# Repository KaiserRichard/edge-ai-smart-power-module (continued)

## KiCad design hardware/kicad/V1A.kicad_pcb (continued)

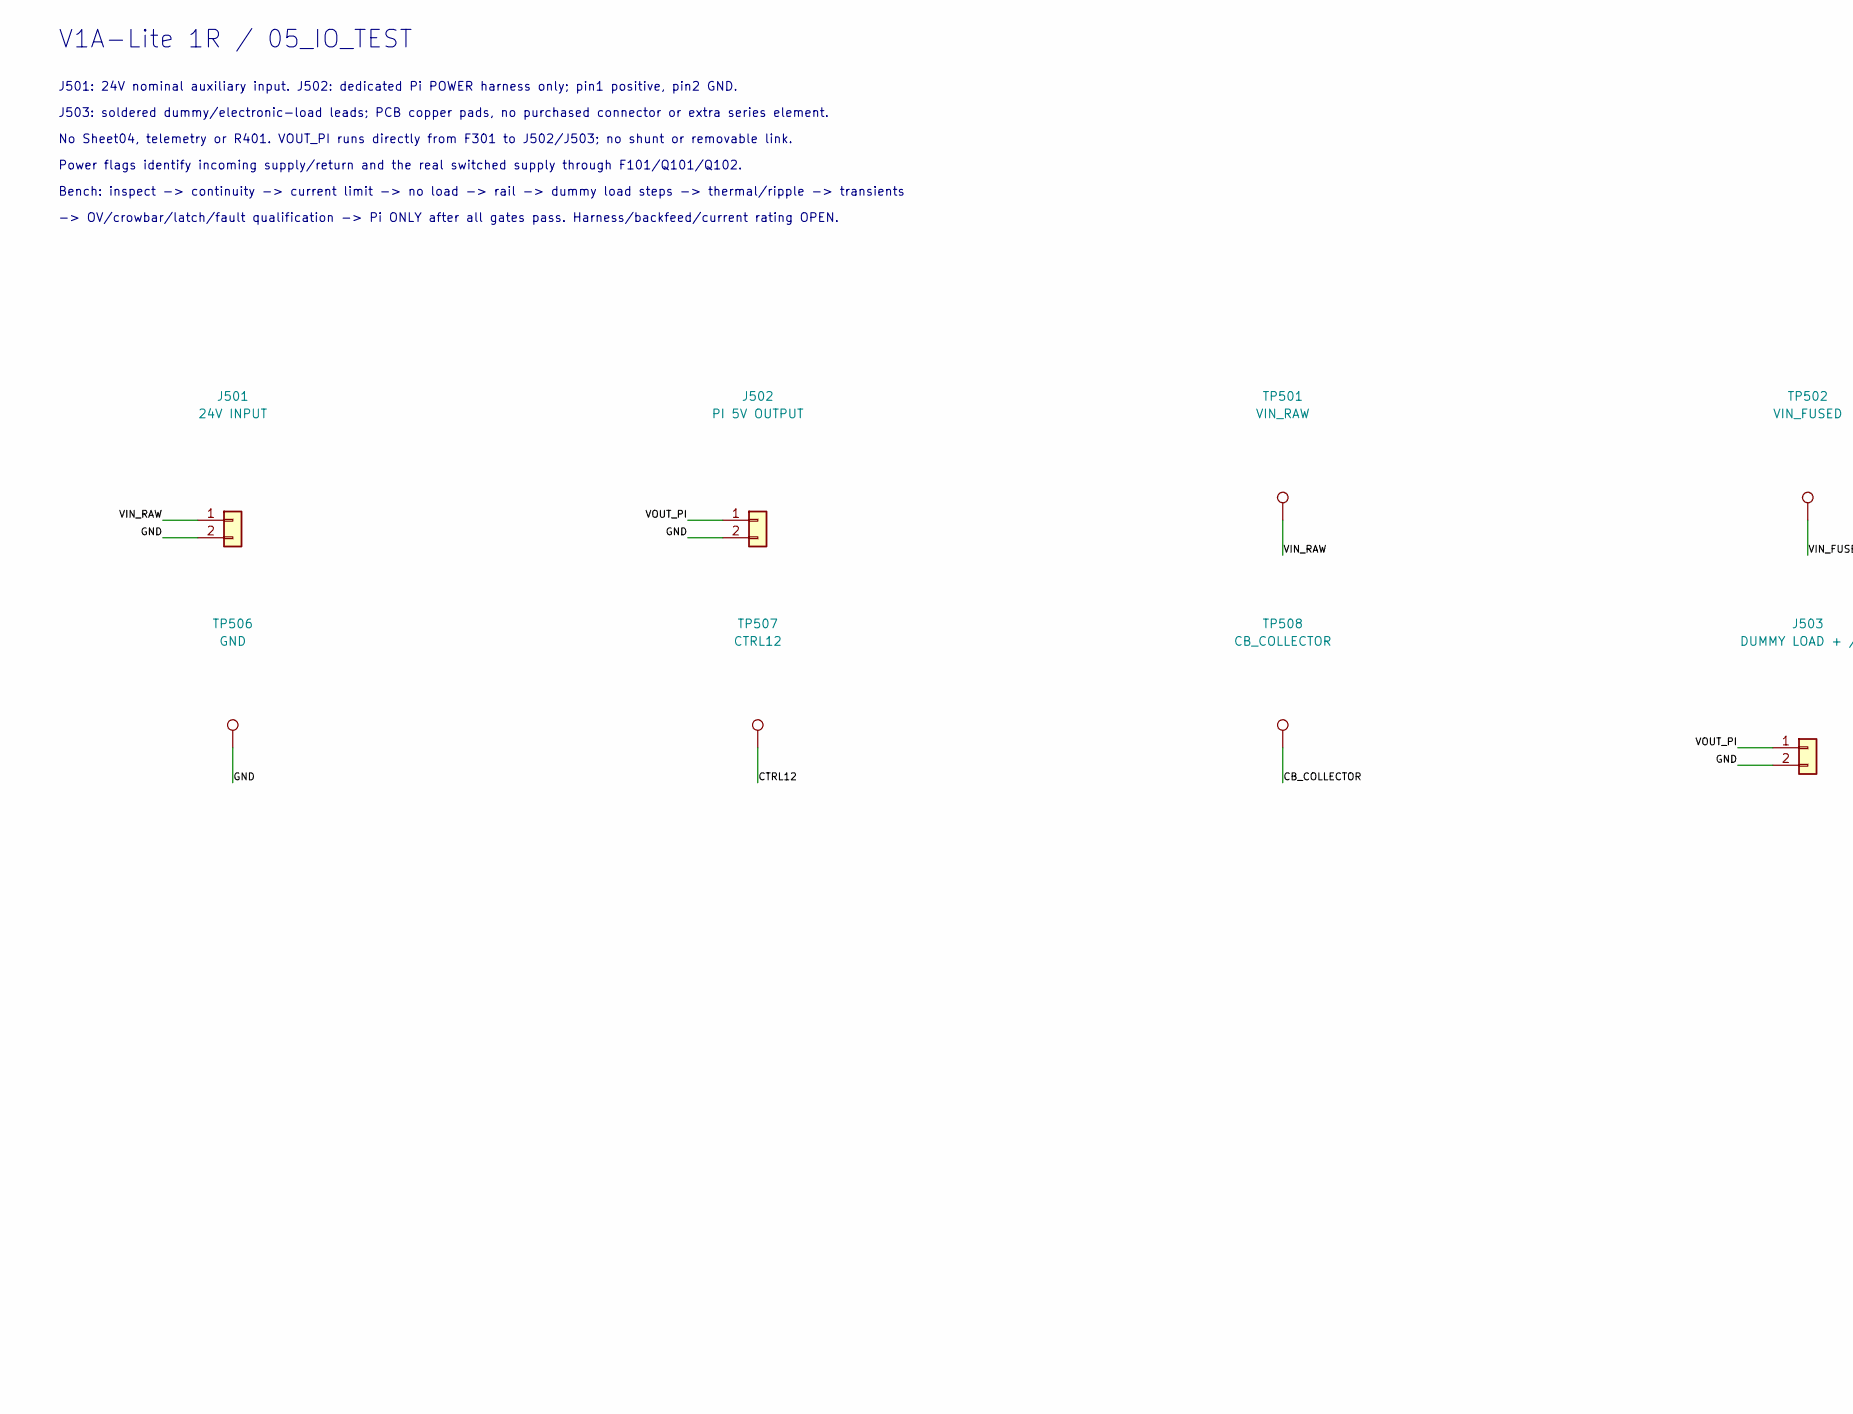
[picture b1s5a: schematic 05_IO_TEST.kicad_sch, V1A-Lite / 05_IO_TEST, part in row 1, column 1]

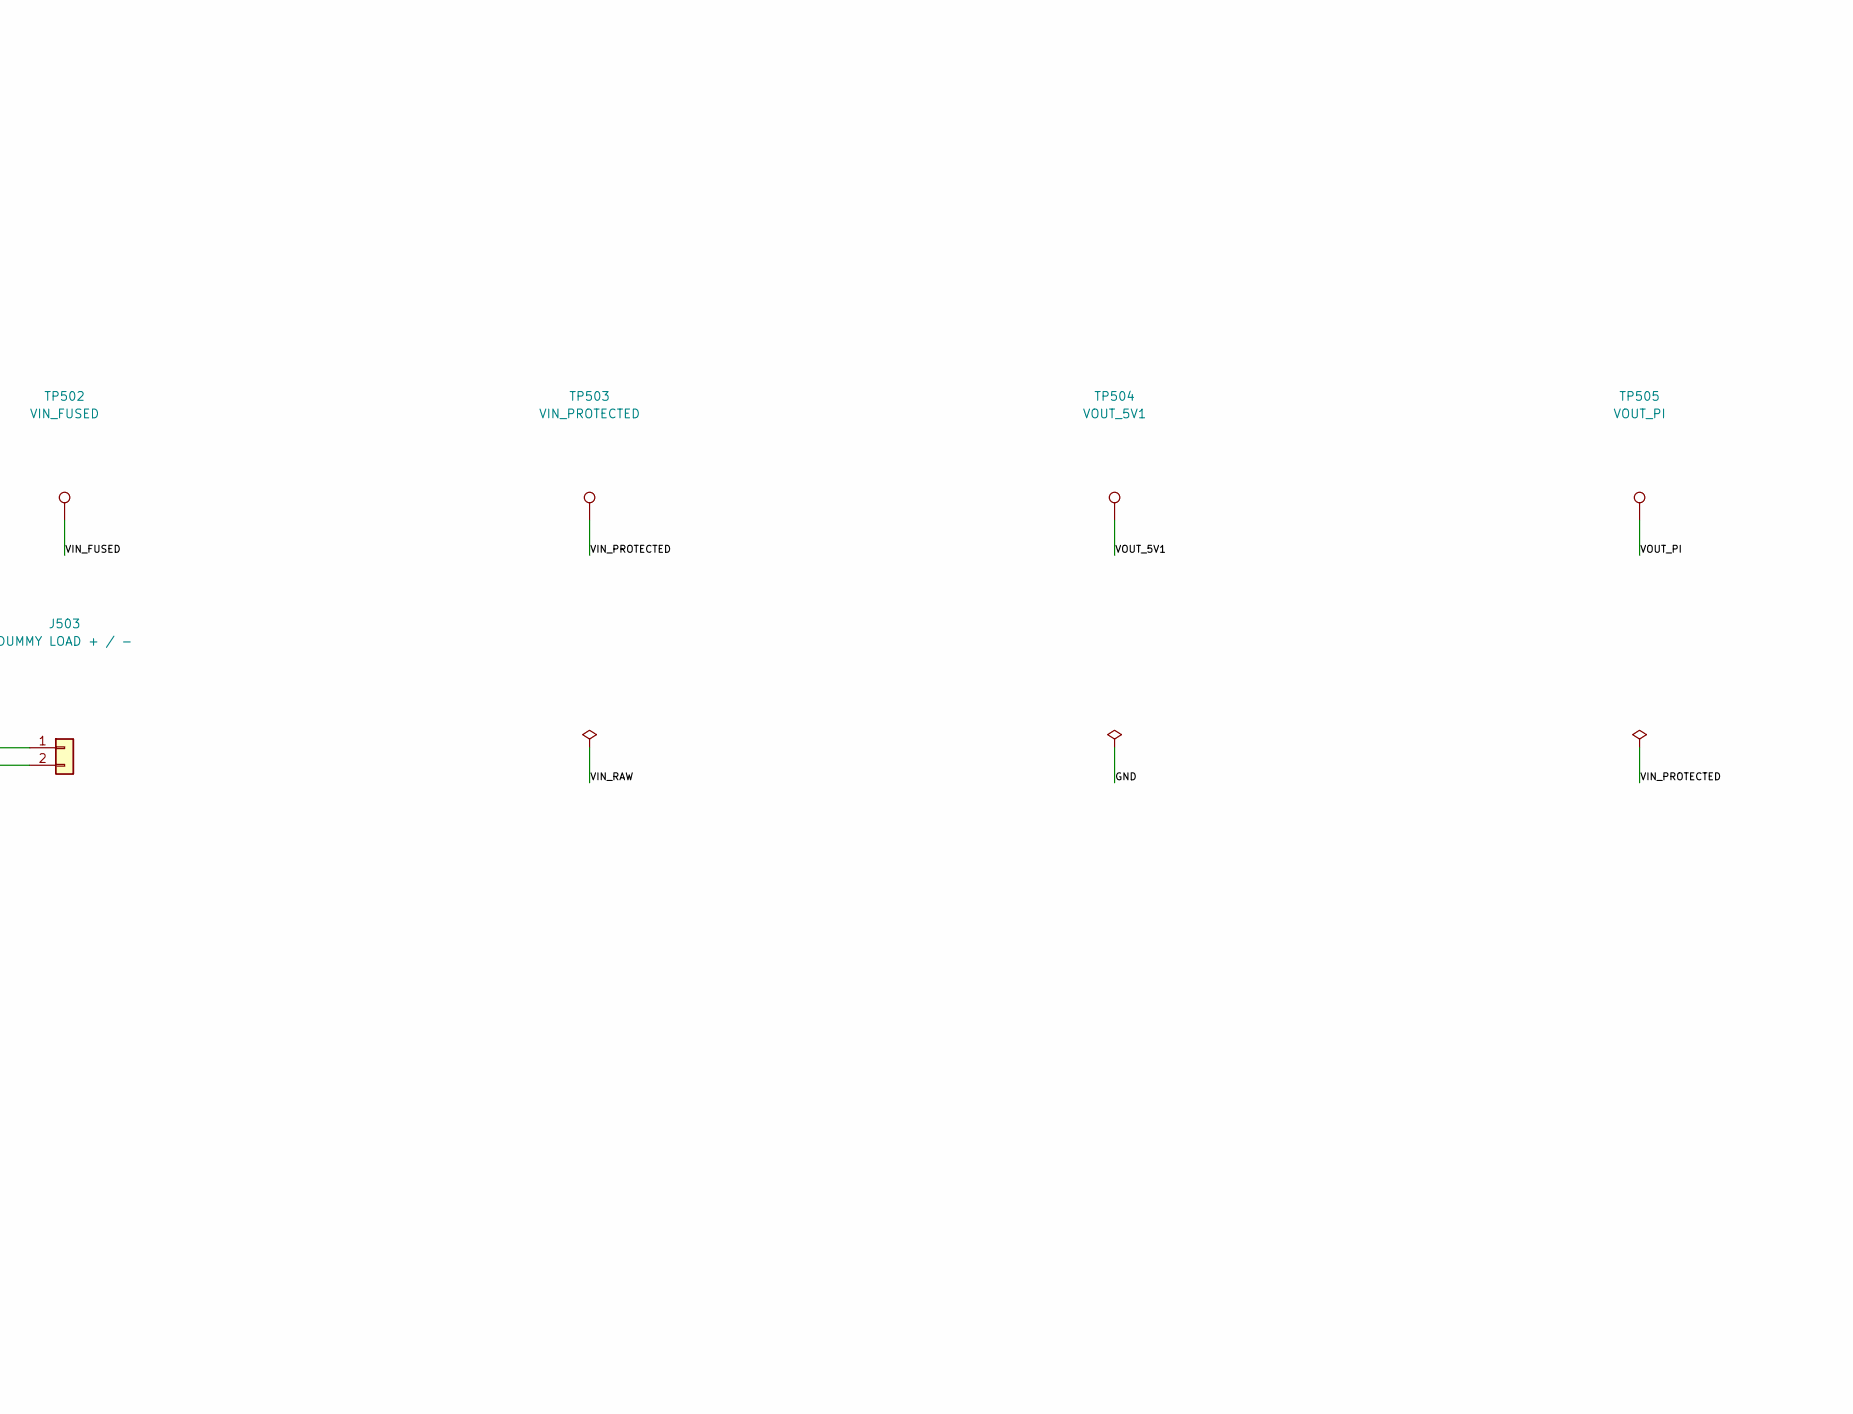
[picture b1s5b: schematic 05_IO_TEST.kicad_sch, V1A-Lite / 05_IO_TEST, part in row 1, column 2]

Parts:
J501: 24V INPUT; JST_B2P_VH_FB_B_P3.96_THT; MPN B2P-VH-FB-B(LF)(SN); LCSC C158006
J502: PI 5V OUTPUT; JST_B2P_VH_FB_B_P3.96_THT; MPN B2P-VH-FB-B(LF)(SN); LCSC C158006
J503: DUMMY LOAD + / -; Dummy_Load_Pads; MPN PCB_FEATURE; LCSC N/A
TP501: VIN_RAW; TestPoint_Pad_D2.0mm; MPN PCB_FEATURE; LCSC N/A
TP502: VIN_FUSED; TestPoint_Pad_D2.0mm; MPN PCB_FEATURE; LCSC N/A
TP503: VIN_PROTECTED; TestPoint_Pad_D2.0mm; MPN PCB_FEATURE; LCSC N/A
TP504: VOUT_5V1; TestPoint_Pad_D2.0mm; MPN PCB_FEATURE; LCSC N/A
TP505: VOUT_PI; TestPoint_Pad_D2.0mm; MPN PCB_FEATURE; LCSC N/A
TP506: GND; TestPoint_Pad_D2.0mm; MPN PCB_FEATURE; LCSC N/A
TP507: CTRL12; TestPoint_Pad_D2.0mm; MPN PCB_FEATURE; LCSC N/A
TP508: CB_COLLECTOR; TestPoint_Pad_D2.0mm; MPN PCB_FEATURE; LCSC N/A

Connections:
/CB_COLLECTOR: TP508.1; also elsewhere on the board
/CTRL12: TP507.1; also elsewhere on the board
/GND: J501.2, J502.2, J503.2, TP506.1; also elsewhere on the board
/VIN_FUSED: TP502.1; also elsewhere on the board
/VIN_PROTECTED: TP503.1; also elsewhere on the board
/VIN_RAW: J501.1, TP501.1; also elsewhere on the board
/VOUT_5V1: TP504.1; also elsewhere on the board
/VOUT_PI: J502.1, J503.1, TP505.1; also elsewhere on the board

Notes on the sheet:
V1A-Lite 1R / 05_IO_TEST
J501: 24V nominal auxiliary input. J502: dedicated Pi POWER harness only; pin1 positive, pin2 GND.
J503: soldered dummy/electronic-load leads; PCB copper pads, no purchased connector or extra series element.
No Sheet04, telemetry or R401. VOUT_PI runs directly from F301 to J502/J503; no shunt or removable link.
Power flags identify incoming supply/return and the real switched supply through F101/Q101/Q102.
Bench: inspect -> continuity -> current limit -> no load -> rail -> dummy load steps -> thermal/ripple -> transients
-> OV/crowbar/latch/fault qualification -> Pi ONLY after all gates pass. Harness/backfeed/current rating OPEN.

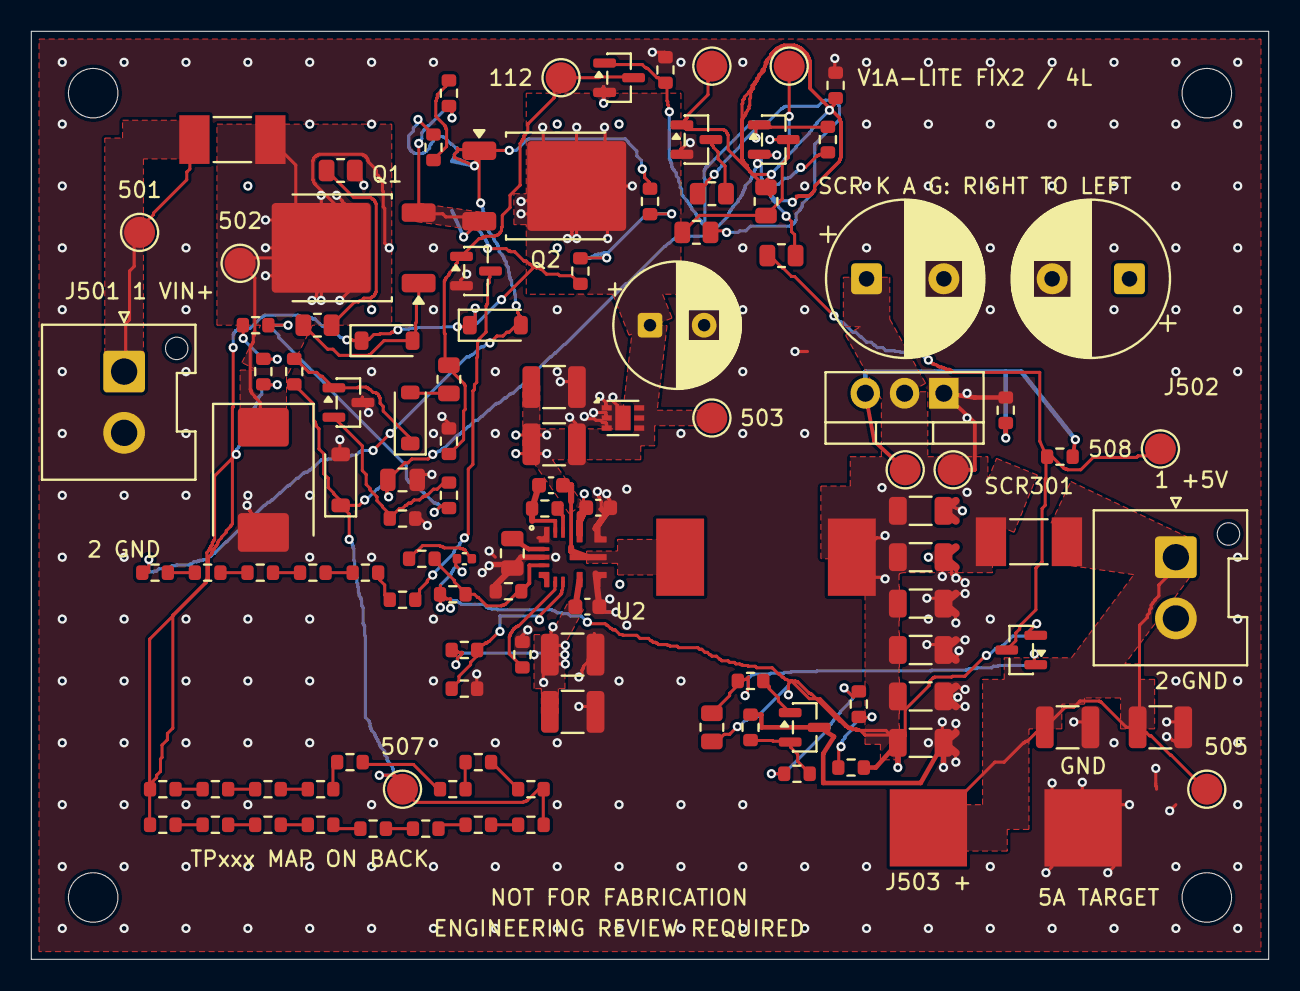
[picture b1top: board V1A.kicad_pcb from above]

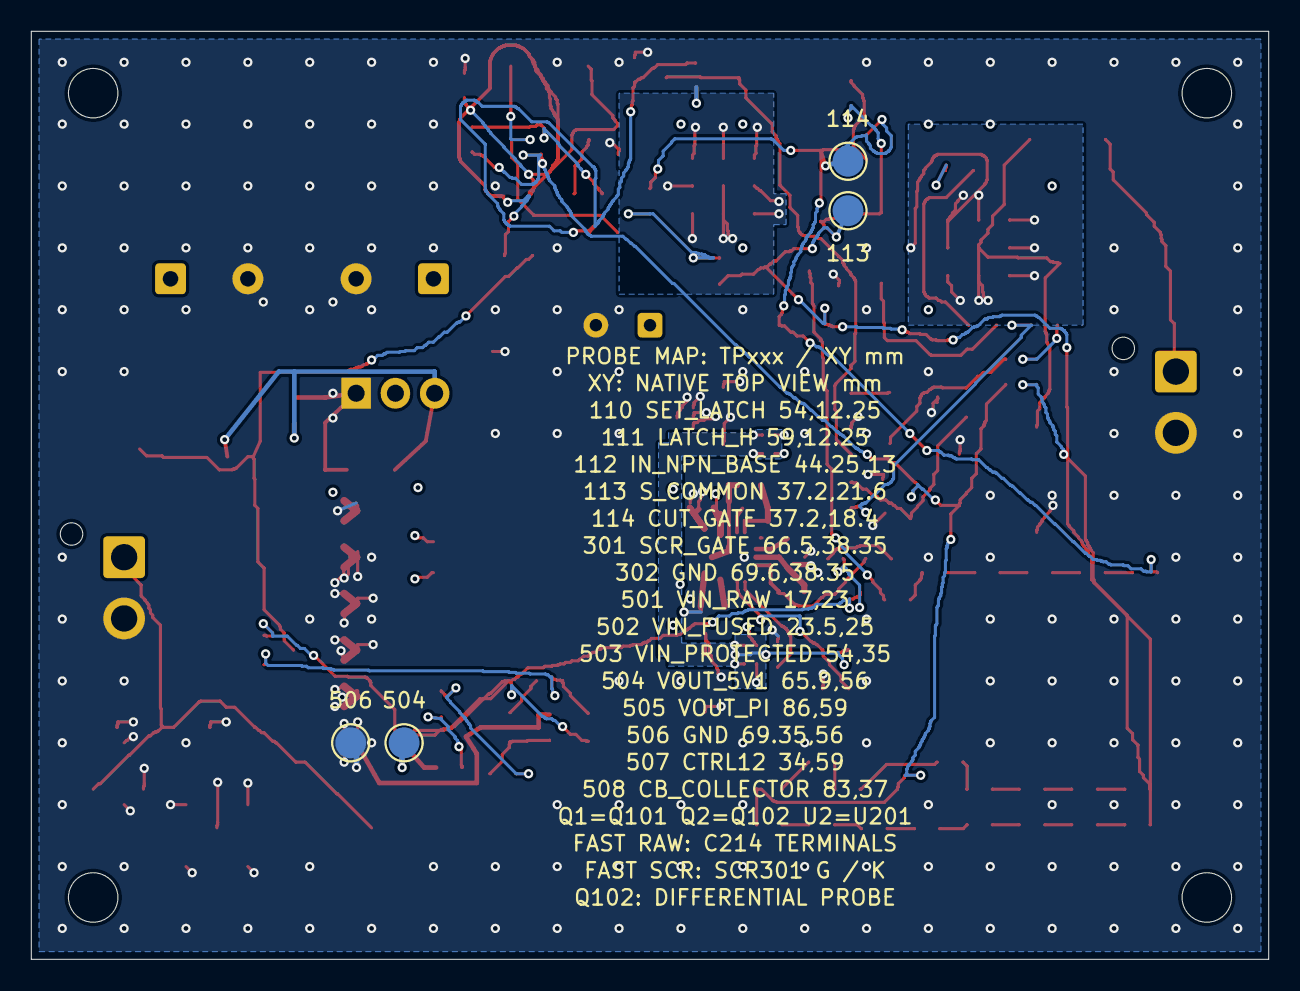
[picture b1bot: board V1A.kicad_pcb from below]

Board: 4 copper layers, 80.0 x 60.0 mm, 120 parts (4 on the bottom side), 59 nets.

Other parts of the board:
MH1, MH2, MH3, MH4: M3 NPTH; MountingHole_3.2mm_M3

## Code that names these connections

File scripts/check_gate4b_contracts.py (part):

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      'J501':['VIN_RAW','GND'], 'J502':['LOAD_5V1','GND'],
      'J503':['GND','3V3_HOST','SDA_HOST','SCL_HOST'],
      'JP501':['LOAD_5V1','LOAD_FIXTURE'], 'TP505':['LOAD_FIXTURE','GND'],
      'PF1':['VIN_RAW'], 'PF2':['VIN_PROTECTED'], 'PF3':['BUCK_SW'], 'PF4':['L201_IN'], 'PF5':['GND'],
    }
    for ref,nn in contracts.items():pins(ref,nn)
    for ref,source,gate,drain in [('Q301','PROT_MID','PROT_GATE','VOUT_5V1'),('Q302','PROT_MID','PROT_GATE','SERIES_OUT'),('Q303','GND','CB_GATE','CB_DRAIN'),('Q330','GND','RAW_DUMP_GATE','RAW_DUMP_DRAIN')]:
        pins(ref,[source]*3+[gate]+[drain]*4)
    for ref,node in [('D102','VIN_PROTECTED'),('D330','VOUT_5V1'),('D331','VOUT_PROTECTED')]:pins(ref,['GND',node,'GND'])
    for ref,a,b in [
      ('JP101','EFUSE_OUT','VIN_PROTECTED'),('JP201','BUCK_SW','L201_IN'),('L201','L201_IN','L201_OUT'),('JP202','L201_OUT','VOUT_5V1'),
      ('JP301','SERIES_OUT','VOUT_PROTECTED'),('JP330','CB_BALLAST_OUT','CB_DRAIN'),('JP331','RAW_BALLAST_OUT','RAW_DUMP_DRAIN'),
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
